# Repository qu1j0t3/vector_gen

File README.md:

# Vector generator

Copyright (C) 2017-2022 Toby Thain <toby@telegraphics.com.au>

## Purpose

This circuit is designed to produce X, Y and Z (blanking) signals
for an analog CRT such as an oscilloscope or XY monitor.

It is controlled by a microcontroller using one digital input
and 12 digital outputs. The speed of the microcontroller is not
critical to the design; all timing critical functions are executed
in hardware.

## Output specifications

### Monitors tested

* Tektronix 602, 603, 604, 606

## Graphic capabilities

* Positioning to 12 bit precision
* Lines (approx 20,000 short-medium vectors per second[1];
  10,000 "long" vectors per second[2])
  - dashed lines (dashing defined by 30 bit vector)
  - speed can be increased further by adjusting integrator passives
    and software optimisations
* Points (37,000-60,000 per second at 0.6µs dwell;
  variable brightness by adjusting dwell time)

[1] "boxes" benchmark
[2] "square" benchmark

Above figures assume:
- integrator input resistor 15 kOhm (this can be decreased, e.g. 4.7kOhm)
- integrator capacitor 10nF
- maximum slew rate approx 0.015 V/µs or draw full deflection in 66µs

## Microcontroller options

Dev board with Arduino Uno pinout. Pins provided for 5V inputs
or level shifted 3.3V inputs.

### Tested ports

* NXP Freedom KE06Z modified for 5V

### Planned ports

* Arduino Duemilanove, Uno
* STM32G474RE (3.3V)
* Adafruit M4 Express

## Power supply

Bipolar +5/-5V. Current approx 30mA (15mA excluding power LED).

Suitable supply from AC mains is Dura Micro MD5122-A1.

## Principle of operation

## Output examples/demos

## Modifications

## Other applications

## Version history

* The first version of the board was produced in a batch of 5 by JLCPCB,
  May 2022. These were all claimed by friends and supporters
  even before the PCBs were delivered.

Original design was conceived in 2017/18.

## Future plans

## Credits

I had assistance from many people, mostly via irc, including:

* `joe_z` & `Wohali` with far greater analog expertise
* `larsb`, who encouraged me to build this as an avenue for using real
  vector displays with software emulators of historical computers
* `asjackson`, fellow hacker and friend
* `genii`, who drilled many holes to work around a position defect
  on the first PCB version

## Dedication

Dedicated to my friend `bootnecklad`, 1995–2018.

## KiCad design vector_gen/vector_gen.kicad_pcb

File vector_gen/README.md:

# Board assembly

## General

- Test points can be installed as needed;
  1.2mm holes suit Digikey 36-4952-ND
- IC orientations are consistent, pin 1 to left looking at front
  with power connection at right.

## Power

- Modular power supply is +5/-5V, Dura Micro MD5122-A1
- Connector J6
- R2: 330R or 270R
- LED D1
- test with +5V & GND on J6
- C6, C8: 100µF electrolytic

## Voltage reference

- U13 LM336
- R1 2.2k
- with power applied, check VREF2.5 test point

## 5V MCU

- install J7, J8, J9, J10
  - Only the 2 GND pins need be soldered for J7

## 3.3V MCU

- install J1, J2, J3, J5
  - Only the 2 GND pins need be soldered for J1
- install U16, U17 level shifting buffers
- install their decoupling caps C19, C20
- install RN2, R29, R30, R33, R3, R28

## Coefficient DACs

- install U1 MCP4922
- check levels with step voltage program (Test 1)

## Integrators

- install U6 - tested with MCP6292
  - needs to be R2R output at least, does not need to be fast, as slew rates are < 0.05V/µs
- caps C11 and C12 must be matched closely.
  - I use an RC Schmitt oscillator and frequency counter to get relative values,
    sort, and take closest pairs.
- install R5, R7
  - these should be closely matched
  - tested between 4.7k (fast) and 15k (slow); should work even faster
    but with more timing error and noise susceptibility (I think)
- install R4, R6

## PCB version 1 bugs

In first version of PCB there is a bug that leaves U6 Vss/Vdd pins floating
and U5 Vdd floating:

- install jumper instead of C10, this connects U6 Vdd to GND
- install C9, and wire between +5V pin of C9 and +5V rail,
  e.g. + pin of C6, or +5V pin of power inlet connector.

Due to redrilling of X and Z BNC footprints:

- Z signal pin should be connected to pin 2 of U19 (analog switch)
  - This can be a wire, or for short circuit protection of the switch,
    a resistor at least 1k. The switch has a current limit of 10mA.
- Z signal pin should also be connected to Z1 test point if needed
- X signal pin should be connected to pin 1 of U8 (output amplifier)

## Switches

- install U5 SN74LV4066AN
- install R34, R35 47R - current limiting resistors
- check integrator run and reset with test program (Test program 2)

## Rest of assembly

- R21: 22k 5%, Z output follower emitter resistor
- R26, R27: 2.2k 5%, pullups for comparators
- Q1: 2N3904 Z follower
- R12, R13: do not install unless needed - provides hysteresis to comparators. Nominal 100kOhm
- C13, C14, C17, C18: Vref filter caps - 1µF but could be increased to 4.7µF later?
- R16: 10kOhm Z divider
- C22, C21, C15, C16, C3, C4, C5, C7, C9, C1, C2: 1µF decoupling caps
- R8, R22: Matched pair which divide Vref to a position offset voltage, can be 15k or 33k
  - In fact the matching doesn't matter very much since the position is user adjustable on the monitor
  - This divider could be a pot if a position adjustment were desired on this board
- R10, R23: Same
- R9, R11: Do not install
- R17, R18: 33k, pair with matched values
- R24: arbitrary 15k
- R19, R20: 33k, pair with matched values
- R25: 15k selected so that ratio of R25 : (R19+R20) closely matches ratio of R24 : (R17+R18)
  - this should make the X and Y gain roughly equal
- install U8 TL072IP summing/output amplifiers
- install U9 LM319 limit comparators
- install U10 MCP4922 position DACs
- install U11 MCP4922 limit DACs
- install U12 CD4019BE AND/OR select
- install U14 74AHC86 quad XOR
- install U19 MAX4544 Z enable switch

## Calibration

### Test 1b - X/Y coefficient zero

* attach ground probe to a ground point on circuit,
  e.g. BNC shroud, or grounded pins of J1 (pins 2, 3 where pin 1 is closest to J3)
* after letting circuit warm up a few minutes, measure the 2.5V reference. e.g. VREF = 2.4897
* run test program 1b (see `main.c`)
* voltages should step through
  * XCOEFF expected: 2.5    actual: 2.4947 (XC)
  * YCOEFF expected: 2.5    actual: 2.4840 (YC)
* note actual voltages above, take differences from VREF, convert to DAC units
  * Noting that Coeff DACS use gain x2 i.e. 1 unit = 5/4096 V
  * XCOEFF adjustment is VREF-XC = 4096*(2.4897-2.4947)/5 = -4
  * YCOEFF adjustment is VREF-YC = 4096*(2.4897-2.4840)/5 = +5
  * Set these values in `display_list.h`, defines `DAC_COEFF_X_ADJ` and `DAC_COEFF_Y_ADJ`

### Test 3 - Z voltage

- Connect DVM ground to ground point (see test 1b)
- Connect DVM + lead to Z test point (if using first version pcb make sure it's connected, see bugs above)
- Run test program 3
- Turn Intensity pot fully CCW, voltage reads 1.628 (measured at pin 1 of U19)
  - at Z output this reads 1.978
- Turn fully CW, voltage reads approx zero
  - at Z output reads approx zero

### Test 4 - Limit DAC offsets - IMPORTANT

- Run test program 4
- Connect DVM ground to ground point (see test 1b)
- Connect DVM + lead to XINTEG test point, measure voltage, e.g. 2.4894 (XI)
- Move DVM + lead to YINTEG test point, measure voltage, e.g. 2.4900 (YI)
- Move DVM + lead to XLIMIT test point, measure voltage, e.g. 2.4955 (XL)
- Move DVM + lead to YLIMIT test point, measure voltage, e.g. 2.5054 (YL)
- Noting that Limit DACS use gain x2 i.e. 1 unit = 5/4096 V
- Compute limit adjustment for X = 4096*(XI - XL)/5 = -5
- adjustment for Y = 4096*(YI - YL)/5 = -13
- Set these values in `display_list.h`, defines `DAC_LIMIT_X_ADJ` and `DAC_LIMIT_Y_ADJ`

- Run test program 4b
- Check that XLIMIT and YLIMIT are within about 2 mV of XINTEG and YINTEG

## Version 2

- add [supply reversal protection](https://twitter.com/gsuberland/status/1348719603799773189)

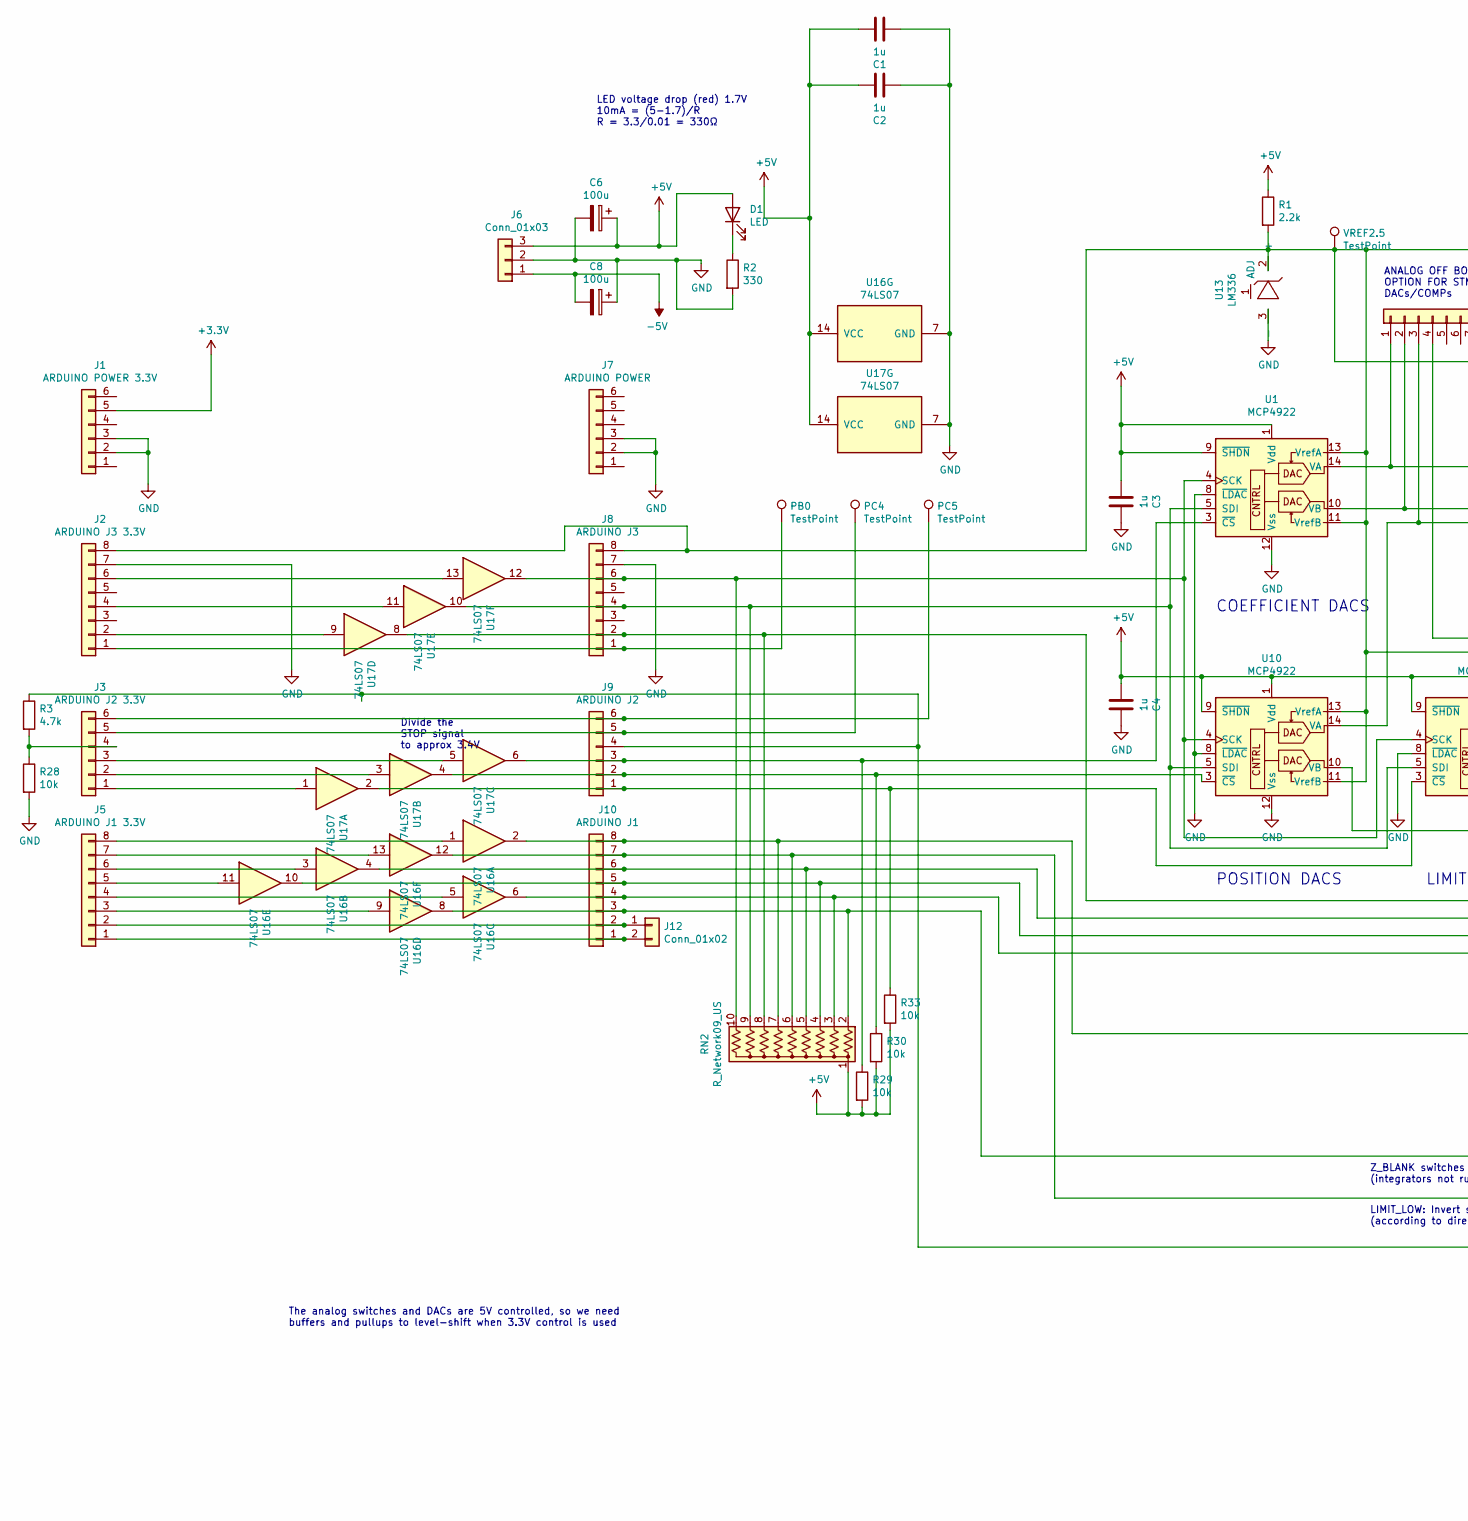
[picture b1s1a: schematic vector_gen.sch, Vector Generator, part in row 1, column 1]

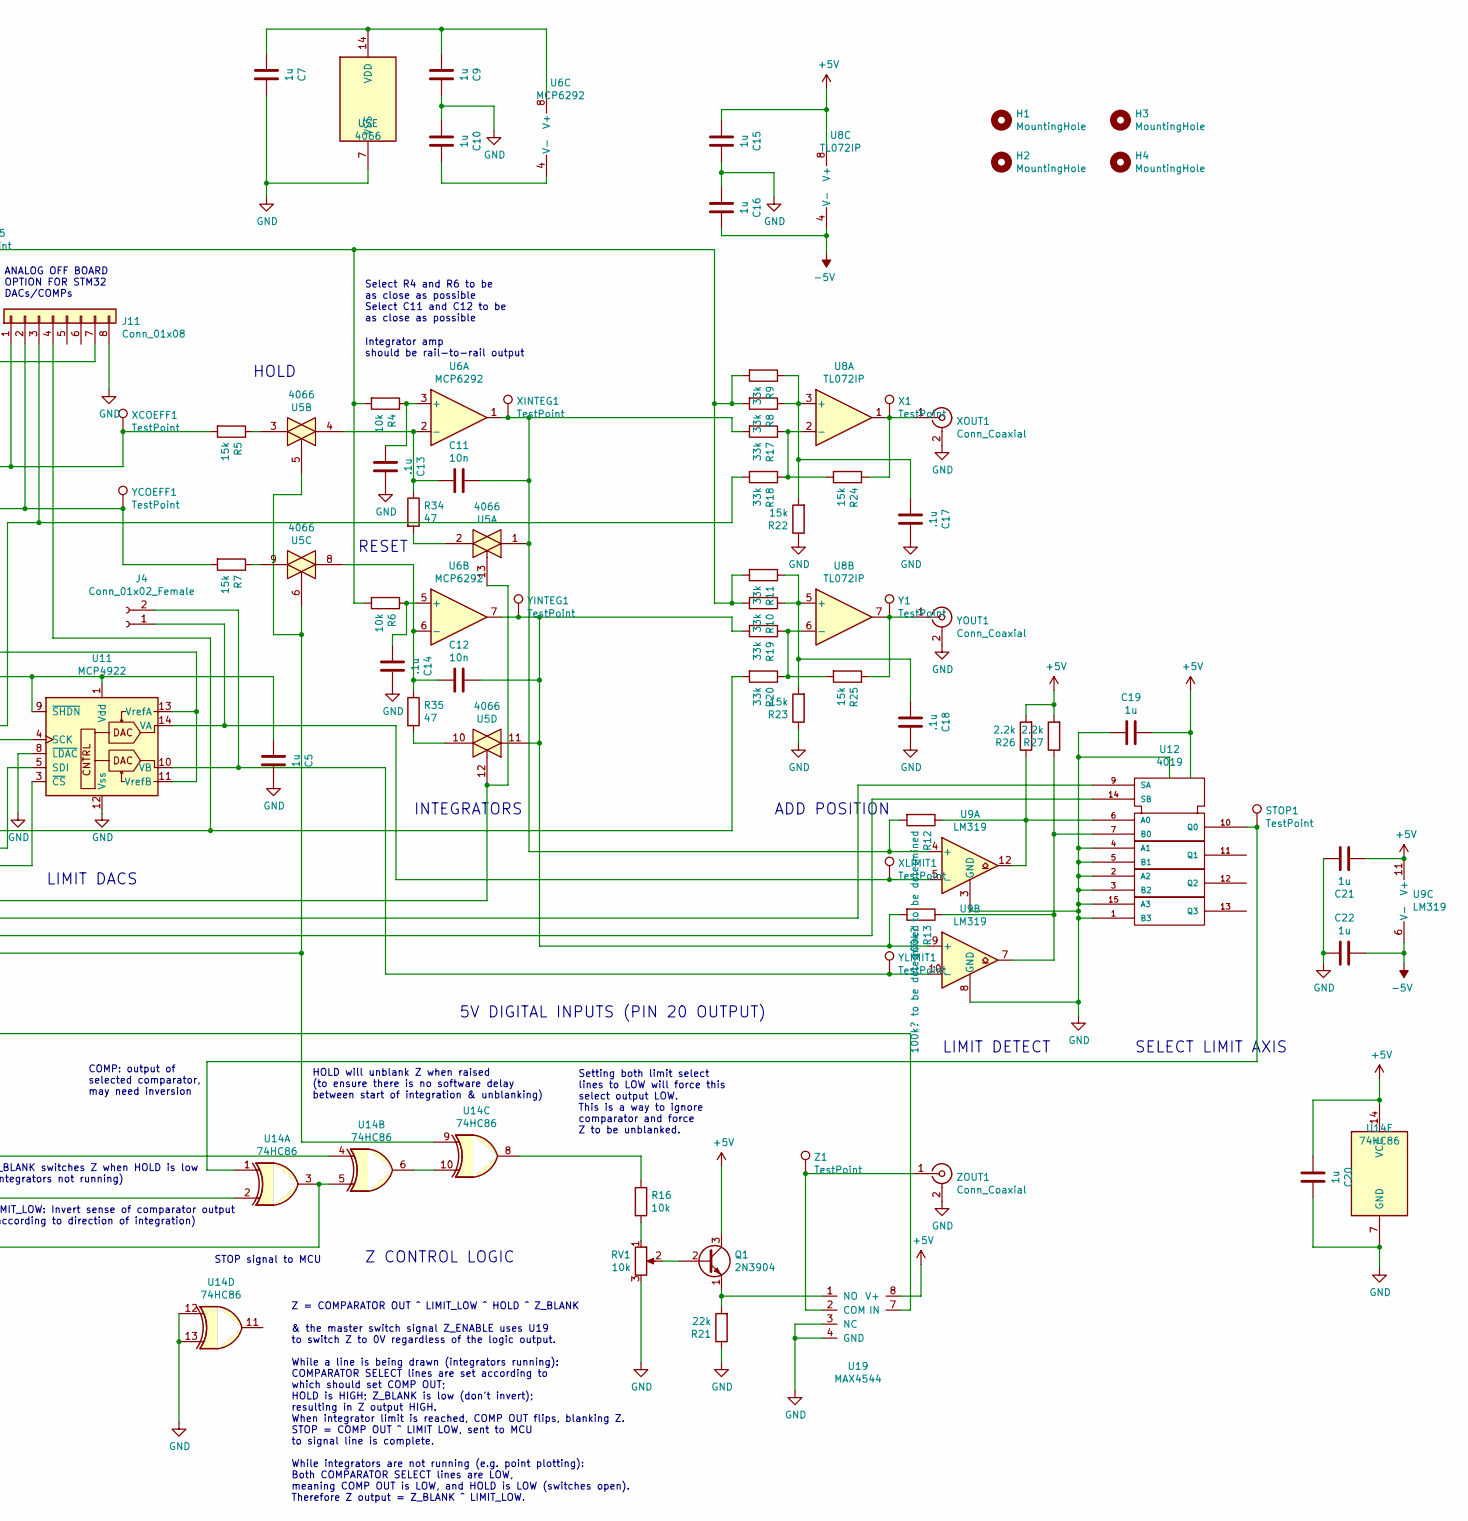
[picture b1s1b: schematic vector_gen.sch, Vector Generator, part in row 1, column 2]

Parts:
C1, C2, C3, C4, C5, C7, C9, C10, C15, C16, C19, C20, C21, C22: 1u; C_Disc_D5.0mm_W2.5mm_P2.50mm
C6, C8: 100u; CP_Radial_D6.3mm_P2.50mm
C11, C12: 10n; C_Rect_L7.0mm_W2.5mm_P5.00mm
C13, C14, C17, C18: .1u; C_Disc_D5.0mm_W2.5mm_P2.50mm
D1: LED; LED_D3.0mm
H1, H2, H3, H4: MountingHole; MountingHole_3.2mm_M3
J1: ARDUINO POWER 3.3V; PinHeader_1x06_P2.54mm_Vertical
J2: ARDUINO J3 3.3V; PinHeader_1x08_P2.54mm_Vertical
J3: ARDUINO J2 3.3V; PinHeader_1x06_P2.54mm_Vertical
J4: Conn_01x02_Female; PinHeader_1x02_P2.54mm_Vertical
J5: ARDUINO J1 3.3V; PinHeader_1x08_P2.54mm_Vertical
J6: Conn_01x03; Molex_KK-396_A-41791-0003_1x03_P3.96mm_Vertical
J7: ARDUINO POWER; PinHeader_1x06_P2.54mm_Vertical
J8: ARDUINO J3; PinHeader_1x08_P2.54mm_Vertical
J9: ARDUINO J2; PinHeader_1x06_P2.54mm_Vertical
J10: ARDUINO J1; PinHeader_1x08_P2.54mm_Vertical
J11: Conn_01x08; PinHeader_1x08_P2.54mm_Vertical
J12: Conn_01x02; PinSocket_1x02_P2.54mm_Vertical
PB0: TestPoint; TestPoint_THTPad_2.5x2.5mm_Drill1.2mm
PC4, PC5: TestPoint; TestPoint_THTPad_2.5x2.5mm_Drill1.2mm
Q1: 2N3904; TO-92_Inline_Wide
R1, R26, R27: 2.2k; R_Axial_DIN0207_L6.3mm_D2.5mm_P10.16mm_Horizontal
R2: 330; R_Axial_DIN0207_L6.3mm_D2.5mm_P10.16mm_Horizontal
R3: 4.7k; R_Axial_DIN0207_L6.3mm_D2.5mm_P10.16mm_Horizontal
R4, R6, R16, R28, R29, R30, R33: 10k; R_Axial_DIN0207_L6.3mm_D2.5mm_P10.16mm_Horizontal
R5, R7, R22, R23, R24, R25: 15k; R_Axial_DIN0207_L6.3mm_D2.5mm_P10.16mm_Horizontal
R8, R9, R10, R11, R17, R18, R19, R20: 33k; R_Axial_DIN0207_L6.3mm_D2.5mm_P10.16mm_Horizontal
R12, R13: 100k? to be determined; R_Axial_DIN0207_L6.3mm_D2.5mm_P10.16mm_Horizontal
R21: 22k; R_Axial_DIN0207_L6.3mm_D2.5mm_P10.16mm_Horizontal
R34, R35: 47; R_Axial_DIN0207_L6.3mm_D2.5mm_P10.16mm_Horizontal
RN2: R_Network09_US; R_Array_SIP10
RV1: 10k; Potentiometer_TT_P0915N
STOP1: TestPoint; TestPoint_THTPad_2.5x2.5mm_Drill1.2mm
U1, U10, U11: MCP4922; DIP-14_W7.62mm_Socket
U5: 4066; DIP-14_W7.62mm_Socket
U6: MCP6292; DIP-8_W7.62mm_Socket
U8: TL072IP; DIP-8_W7.62mm_Socket
U9: LM319; DIP-14_W7.62mm_Socket
U12: 4019; DIP-16_W7.62mm_Socket
U13: LM336; TO-92_HandSolder
U14: 74HC86; DIP-14_W7.62mm_Socket
U16, U17: 74LS07; DIP-14_W7.62mm_Socket
U19: MAX4544; DIP-8_W7.62mm_Socket
VREF2.5: TestPoint; TestPoint_THTPad_2.5x2.5mm_Drill1.2mm
X1: TestPoint; TestPoint_THTPad_2.5x2.5mm_Drill1.2mm
XCOEFF1: TestPoint; TestPoint_THTPad_2.5x2.5mm_Drill1.2mm
XINTEG1: TestPoint; TestPoint_THTPad_2.5x2.5mm_Drill1.2mm
XLIMIT1: TestPoint; TestPoint_THTPad_2.5x2.5mm_Drill1.2mm
XOUT1: Conn_Coaxial; BNC_TEConnectivity_1478204_Vertical
Y1: TestPoint; TestPoint_THTPad_2.5x2.5mm_Drill1.2mm
YCOEFF1: TestPoint; TestPoint_THTPad_2.5x2.5mm_Drill1.2mm
YINTEG1: TestPoint; TestPoint_THTPad_2.5x2.5mm_Drill1.2mm
YLIMIT1: TestPoint; TestPoint_THTPad_2.5x2.5mm_Drill1.2mm
YOUT1: Conn_Coaxial; BNC_TEConnectivity_1478204_Vertical
Z1: TestPoint; TestPoint_THTPad_2.5x2.5mm_Drill1.2mm
ZOUT1: Conn_Coaxial; BNC_TEConnectivity_1478204_Vertical

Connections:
+3V3: J1.5
+5V: C1.1, C2.1, C3.2, C4.2, C5.2, C6.1, C15.2, C19.1, C20.2, C21.2, D1.2 (A), J6.3, Q1.3 (C), R1.1, R26.2, R27.2, R29.2, R30.2, R33.2, RN2.1 (common), U1.1 (Vdd), U1.9 (~SHDN), U8.8 (V+), U9.11 (V+), U10.1 (Vdd), U10.9 (~SHDN), U11.1 (Vdd), U11.9 (~SHDN), U12.16 (Vdd), U14.14 (VCC), U16.14 (VCC), U17.14 (VCC), U19.8 (V+)
-5V: C8.2, C16.1, C22.1, J6.1, U8.4 (V-), U9.6 (V-)
GND: C1.2, C2.2, C3.1, C4.1, C5.1, C6.2, C7.1, C8.1, C9.1, C10.2, C13.1, C14.1, C15.1, C16.2, C17.1, C18.1, C19.2, C20.1, C21.1, C22.2, J1.2, J1.3, J2.7, J6.2, J7.2, J7.3, J8.7, J11.8, R2.2, R21.1, R22.1, R23.1, R28.2, RV1.3, U1.8 (~LDAC), U1.12 (Vss), U5.7 (VSS), U9.3 (GND), U9.8 (GND), U10.8 (~LDAC), U10.12 (Vss), U11.8 (~LDAC), U11.12 (Vss), U12.1 (B3), U12.2 (A2), U12.3 (B2), U12.4 (A1), U12.5 (B1), U12.8 (Vss), U12.15 (A3), U13.3 (-), U14.7 (GND), U14.12, U14.13, U16.7 (GND), U17.7 (GND), U19.3 (NC), U19.4 (GND), XOUT1.2 (Ext), YOUT1.2 (Ext), ZOUT1.2 (Ext)
unnamed: C7.2, C9.2, U5.14 (VDD), U6.8 (V+)
unnamed: C10.1, U6.4 (V-)
unnamed: C11.1, R12.2, R17.2, U5.1, U6.1, U9.4 (+), XINTEG1.1
unnamed: C11.2, R34.1, U5.4, U6.2 (-)
unnamed: C12.1, R13.2, R19.2, U5.11, U6.7, U9.9 (+), YINTEG1.1
unnamed: C12.2, R35.1, U5.8, U6.6 (-)
unnamed: C13.2, R4.1, U6.3 (+)
unnamed: C14.2, R6.1, U6.5 (+)
unnamed: C17.2, R8.1, R9.1, R22.2, U8.3 (+)
unnamed: C18.2, R10.1, R11.1, R23.2, U8.5 (+)
unnamed: D1.1 (K), R2.1
unnamed: J2.1, J8.1, PB0.1
unnamed: J2.2, U17.9
unnamed: J2.4, U17.11
unnamed: J2.6, U17.13
unnamed: J3.1, U17.1
unnamed: J3.2, U17.3
unnamed: J3.3, U17.5
unnamed: J3.4, R3.2, R28.1
unnamed: J3.5, J9.5, PC4.1
unnamed: J3.6, J9.6, PC5.1
unnamed: J4.1, U9.5 (-), U11.14 (VA), XLIMIT1.1
unnamed: J4.2, U9.10 (-), U11.10 (VB), YLIMIT1.1
unnamed: J5.3, U16.9
unnamed: J5.4, U16.5
unnamed: J5.5, U16.11
unnamed: J5.6, U16.3
unnamed: J5.7, U16.13
unnamed: J5.8, U16.1
unnamed: J8.2, RN2.8 (R7), U5.12, U5.13, U17.8
unnamed: J8.4, RN2.9 (R8), U1.5 (SDI), U10.5 (SDI), U11.5 (SDI), U17.10
unnamed: J8.6, RN2.10 (R9), U1.4 (SCK), U10.4 (SCK), U11.4 (SCK), U17.12
unnamed: J9.1, R33.1, U11.3 (~CS), U17.2
unnamed: J9.2, R30.1, U10.3 (~CS), U17.4
unnamed: J9.3, R29.1, U1.3 (~CS), U17.6
unnamed: J9.4, R3.1, U14.3, U14.5
unnamed: J5.1, J10.1, J12.2
unnamed: J5.2, J10.2, J12.1
unnamed: J10.3, RN2.2 (R1), U14.4, U16.8
unnamed: J10.4, RN2.3 (R2), U5.5, U5.6, U14.9, U16.6
unnamed: J10.5, RN2.4 (R3), U12.14 (SB), U16.10
unnamed: J10.6, RN2.5 (R4), U12.9 (SA), U16.4
unnamed: J10.7, RN2.6 (R5), U14.2, U16.12
unnamed: J10.8, RN2.7 (R6), U16.2, U19.7 (IN)
unnamed: J11.1, R5.2, U1.14 (VA), XCOEFF1.1
unnamed: J11.2, R7.2, U1.10 (VB), YCOEFF1.1
unnamed: J11.3, R18.2, U10.14 (VA)
unnamed: J11.4, R20.2, U10.10 (VB)
unnamed: J2.8, J8.8, J11.7, R1.2, R4.2, R6.2, R8.2, R9.2, R10.2, R11.2, U1.11 (VrefB), U1.13 (VrefA), U10.11 (VrefB), U10.13 (VrefA), U11.11 (VrefB), U11.13 (VrefA), U13.2 (+), VREF2.5.1
unnamed: Q1.1 (E), R21.2, U19.1 (NO)
unnamed: Q1.2 (B), RV1.2
unnamed: R5.1, U5.3
unnamed: R7.1, U5.9
unnamed: R12.1, R26.1, U9.12, U12.6 (A0)
unnamed: R13.1, R27.1, U9.7, U12.7 (B0)
unnamed: R16.1, U14.8
unnamed: R16.2, RV1.1
unnamed: R17.1, R18.1, R24.2, U8.2 (-)
unnamed: R19.1, R20.1, R25.2, U8.6 (-)
unnamed: R24.1, U8.1, X1.1, XOUT1.1 (In)
unnamed: R25.1, U8.7, Y1.1, YOUT1.1 (In)
unnamed: R34.2, U5.2
unnamed: R35.2, U5.10
unnamed: STOP1.1, U12.10 (Q0), U14.1
unnamed: U14.6, U14.10
unnamed: U19.2 (COM), Z1.1, ZOUT1.1 (In)

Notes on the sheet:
Select R4 and R6 to be as close as possible Select C11 and C12 to be as close as possible
Integrator amp should be rail-to-rail output
COEFFICIENT DACS
ANALOG OFF BOARD OPTION FOR STM32 DACs/COMPs
5V DIGITAL INPUTS (PIN 20 OUTPUT)
RESET
HOLD
Setting both limit select lines to LOW will force this select output LOW. This is a way to ignore comparator and force Z to be unblanked.
SELECT LIMIT AXIS
LIMIT DETECT
ADD POSITION
INTEGRATORS
LIMIT DACS
POSITION DACS
LIMIT_LOW: Invert sense of comparator output (according to direction of integration)
HOLD will unblank Z when raised (to ensure there is no software delay between start of integration & unblanking)
STOP signal to MCU
Z_BLANK switches Z when HOLD is low (integrators not running)
Z = COMPARATOR OUT ^ LIMIT_LOW ^ HOLD ^ Z_BLANK & the master switch signal Z_ENABLE uses U19 to switch Z to 0V regardless of the logic output. While a line is being drawn (integrators running): COMPARATOR SELECT lines are set according to which should set COMP OUT; HOLD is HIGH; Z_BLANK is low (don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
Z CONTROL LOGIC
The analog switches and DACs are 5V controlled, so we need buffers and pullups to level-shift when 3.3V control is used
Divide the STOP signal to approx 3.4V
COMP: output of selected comparator, may need inversion
LED voltage drop (red) 1.7V 10mA = (5-1.7)/R R = 3.3/0.01 = 330Ω

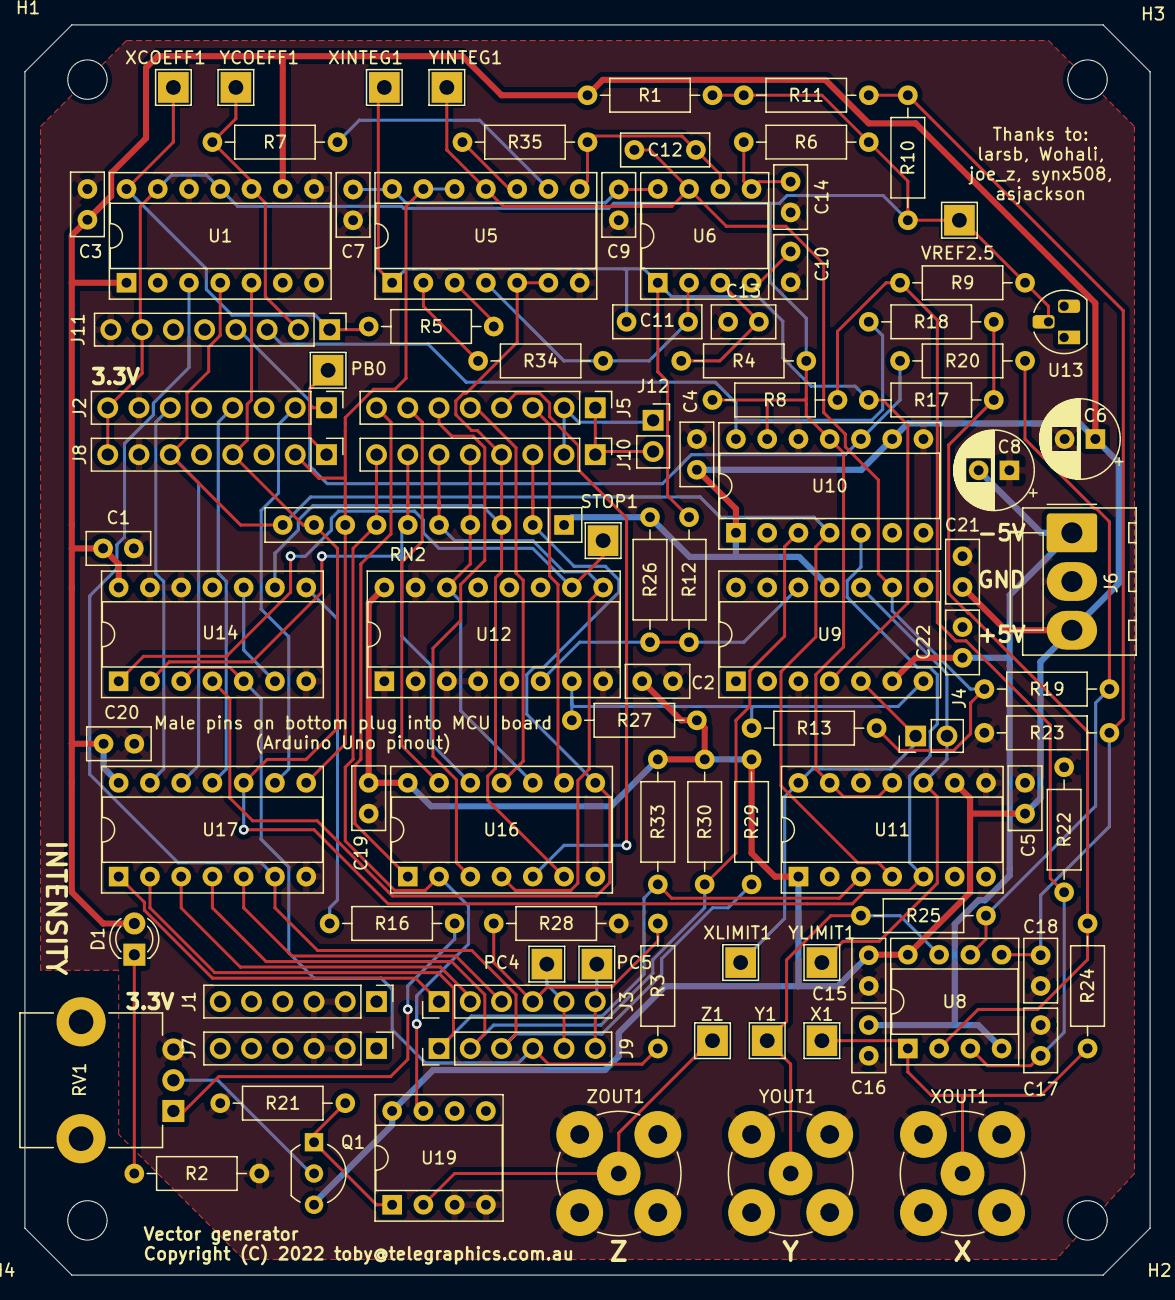
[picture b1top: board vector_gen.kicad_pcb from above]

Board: 2 copper layers, 91.4 x 101.6 mm, 103 parts (0 on the bottom side), 69 nets.

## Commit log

2022-02-08 Initial commit with Kicad project.
2022-02-09 More additions.
2022-02-11 Update with analog option connector, power connector, etc.
2022-02-21 Updates.
2022-03-07 Replace Yamaha DACs with MCP4922 for coefficients.
2022-03-27 Snapshot of work in progress pcb.
2022-04-22 PCB almost routed.
2022-04-23 More routing.
2022-04-24 Rerrange layout
2022-04-28 Ground plane done?
2022-05-03 Add fill to front copper and suggestions from joe_z.
2022-05-03 Fix a connectivity issue.
2022-05-07 Updated.
2022-05-08 Some important corrections. OSHpark candidate?
2022-05-09 New OSHPark manuf candidate.
2022-05-10 New manuf candidate.
2022-05-11 Final JLPCB order.
2022-05-27 Add README
2022-05-27 Updates to README
2022-05-29 Initial commit.
2022-05-29 SPI DAC working.
2022-06-02 Add pcb assembly notes.
2022-06-06 Tested integrators.
2022-06-11 Assembly updates.
2022-06-17 WIP. Port to Arduino.
2022-07-18 First version tested on display.
2022-07-18 Add boxes and maze demos.
2022-07-18 Upgrade maze demo to 18x18
2022-07-18 Add test program and instructions for Limit DAC calibration.
2022-07-18 Tweak maze demo.
2022-07-20 Missed files.
2022-07-20 Refactor to use struct for vector data, allowing heap allocation for 'polygons'.
2022-07-20 Add new 'rocks' demo. :)
2022-07-31 Work in progress on interrupt driven drawing.
2022-08-01 Tweak dashing code. Add serial port code and interactive DAC limit calibration (in 'boxes' demo).
2022-08-01 Make 'rocks' demo semi-interactive, hit space to regenerate display list with new random seed.
2022-08-26 Starburst demo.
2022-08-29 Horizontal line demo.

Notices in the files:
vector_gen/vector_gen.kicad_pcb:
Copyright (C) 2022 toby@telegraphics.com.au
vector_gen/vector_gen.sch:
© toby@telegraphics.com.au 2022
